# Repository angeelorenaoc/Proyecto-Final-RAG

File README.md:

# Proyecto-Final-RAG
Este proyecto tiene como objetivo desarrollar un robot guía autónomo para el pasillo del bloque 18 de la universidad. Diseñado para mejorar la experiencia de los estudiantes nuevos y visitantes, el robot proporcionará información útil y rutas. Él estará equipado con una pantalla OLED y un teclado, facilitando la interacción con los usuarios.

### Diagrama de Bloques: Estructura de Hardware

### Materiales 
  *  Pantalla OLED.
  *  Balizas: Antenas XBEE PRO.
  *  Raspberry Pi pico

### Diagrama de Flujo: Estructura del Código

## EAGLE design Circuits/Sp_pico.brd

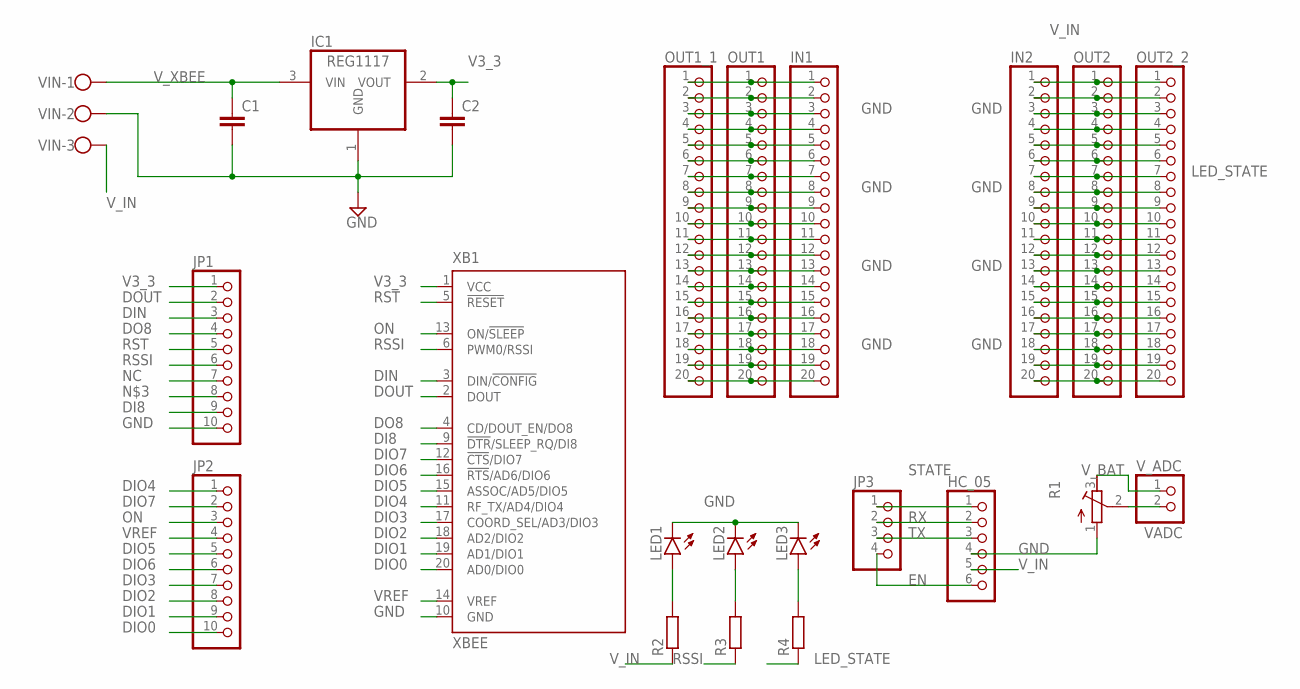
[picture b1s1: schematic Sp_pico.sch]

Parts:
C1, C2: C2.5/5; C2.5-5
HC_05: PINHD-1X6; 1X06
IC1: REG1117; SOT223
IN1, IN2: PINHD-1X20; 1X20
JP1, JP2: PINHD-1X10; 1X10
JP3: PINHD-1X4; 1X04
LED1, LED2, LED3: LED5MM
OUT1, OUT1_1, OUT2, OUT2_2: PINHD-1X20; 1X20
R1: R-TRIMM3296X; RTRIM3296X
R2, R3, R4: R-EU_0204/7; 0204/7
VIN: W237-103
V_ADC: PINHD-1X2; 1X02
XB1: XBEE

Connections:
DI8: JP1.9, XB1.9 (!DTR!/SLEEP_RQ/DI8)
DIN: JP1.3, XB1.3 (DIN/!CONFIG)
DIO0: JP2.10, XB1.20 (AD0/DIO0)
DIO1: JP2.9, XB1.19 (AD1/DIO1)
DIO2: JP2.8, XB1.18 (AD2/DIO2)
DIO3: JP2.7, XB1.17 (COORD_SEL/AD3/DIO3)
DIO4: JP2.1, XB1.11 (RF_TX/AD4/DIO4)
DIO5: JP2.5, XB1.15 (ASSOC/AD5/DIO5)
DIO6: JP2.6, XB1.16 (!RTS!/AD6/DIO6)
DIO7: JP2.2, XB1.12 (!CTS!/DIO7)
DO8: JP1.4, XB1.4 (CD/DOUT_EN/DO8)
DOUT: JP1.2, XB1.2 (DOUT)
EN: HC_05.6, JP3.4
GND: C1.2, C2.2, HC_05.4, IC1.1 (GND), IN1.3, IN1.8, IN1.13, IN1.18, IN2.3, IN2.8, IN2.13, IN2.18, JP1.10, LED1.K (C), LED2.K (C), LED3.K (C), OUT1.3, OUT1.8, OUT1.13, OUT1.18, OUT1_1.3, OUT1_1.8, OUT1_1.13, OUT1_1.18, OUT2.3, OUT2.8, OUT2.13, OUT2.18, OUT2_2.3, OUT2_2.8, OUT2_2.13, OUT2_2.18, R1.1 (A), VIN.2, XB1.10 (GND)
LED_STATE: IN2.7, OUT2.7, OUT2_2.7, R4.1
unnamed: IN1.1, OUT1.1, OUT1_1.1
unnamed: IN1.2, OUT1.2, OUT1_1.2
unnamed: IN1.4, OUT1.4, OUT1_1.4
unnamed: IN1.5, OUT1.5, OUT1_1.5
unnamed: IN1.6, OUT1.6, OUT1_1.6
unnamed: IN1.7, OUT1.7, OUT1_1.7
unnamed: LED1.A, R2.2
unnamed: IN1.9, OUT1.9, OUT1_1.9
unnamed: IN1.10, OUT1.10, OUT1_1.10
unnamed: IN1.11, OUT1.11, OUT1_1.11
unnamed: IN1.12, OUT1.12, OUT1_1.12
unnamed: LED2.A, R3.2
unnamed: IN1.14, OUT1.14, OUT1_1.14
unnamed: IN1.15, OUT1.15, OUT1_1.15
unnamed: IN1.16, OUT1.16, OUT1_1.16
unnamed: IN1.17, OUT1.17, OUT1_1.17
unnamed: LED3.A, R4.2
unnamed: IN1.19, OUT1.19, OUT1_1.19
unnamed: IN1.20, OUT1.20, OUT1_1.20
unnamed: IN2.2, OUT2.2, OUT2_2.2
unnamed: IN2.4, OUT2.4, OUT2_2.4
unnamed: IN2.5, OUT2.5, OUT2_2.5
unnamed: IN2.6, OUT2.6, OUT2_2.6
unnamed: IN2.9, OUT2.9, OUT2_2.9
unnamed: IN2.10, OUT2.10, OUT2_2.10
unnamed: IN2.11, OUT2.11, OUT2_2.11
unnamed: IN2.12, OUT2.12, OUT2_2.12
unnamed: IN2.14, OUT2.14, OUT2_2.14
unnamed: IN2.15, OUT2.15, OUT2_2.15
unnamed: IN2.16, OUT2.16, OUT2_2.16
unnamed: IN2.17, OUT2.17, OUT2_2.17
unnamed: IN2.19, OUT2.19, OUT2_2.19
unnamed: IN2.20, OUT2.20, OUT2_2.20
NC: JP1.7
ON: JP2.3, XB1.13 (ON/!SLEEP)
RSSI: JP1.6, R3.1, XB1.6 (PWM0/RSSI)
RST: JP1.5, XB1.5 (!RESET)
RX: HC_05.2, JP3.2
STATE: HC_05.1, JP3.1
TX: HC_05.3, JP3.3
V3_3: C2.1, IC1.2 (VOUT), JP1.1, XB1.1 (VCC)
VADC: R1.2 (S), V_ADC.2
VREF: JP2.4, XB1.14 (VREF)
V_BAT: R1.3 (E), V_ADC.1
V_IN: HC_05.5, IN2.1, OUT2.1, OUT2_2.1, R2.1, VIN.3
V_XBEE: C1.1, IC1.3 (VIN), VIN.1

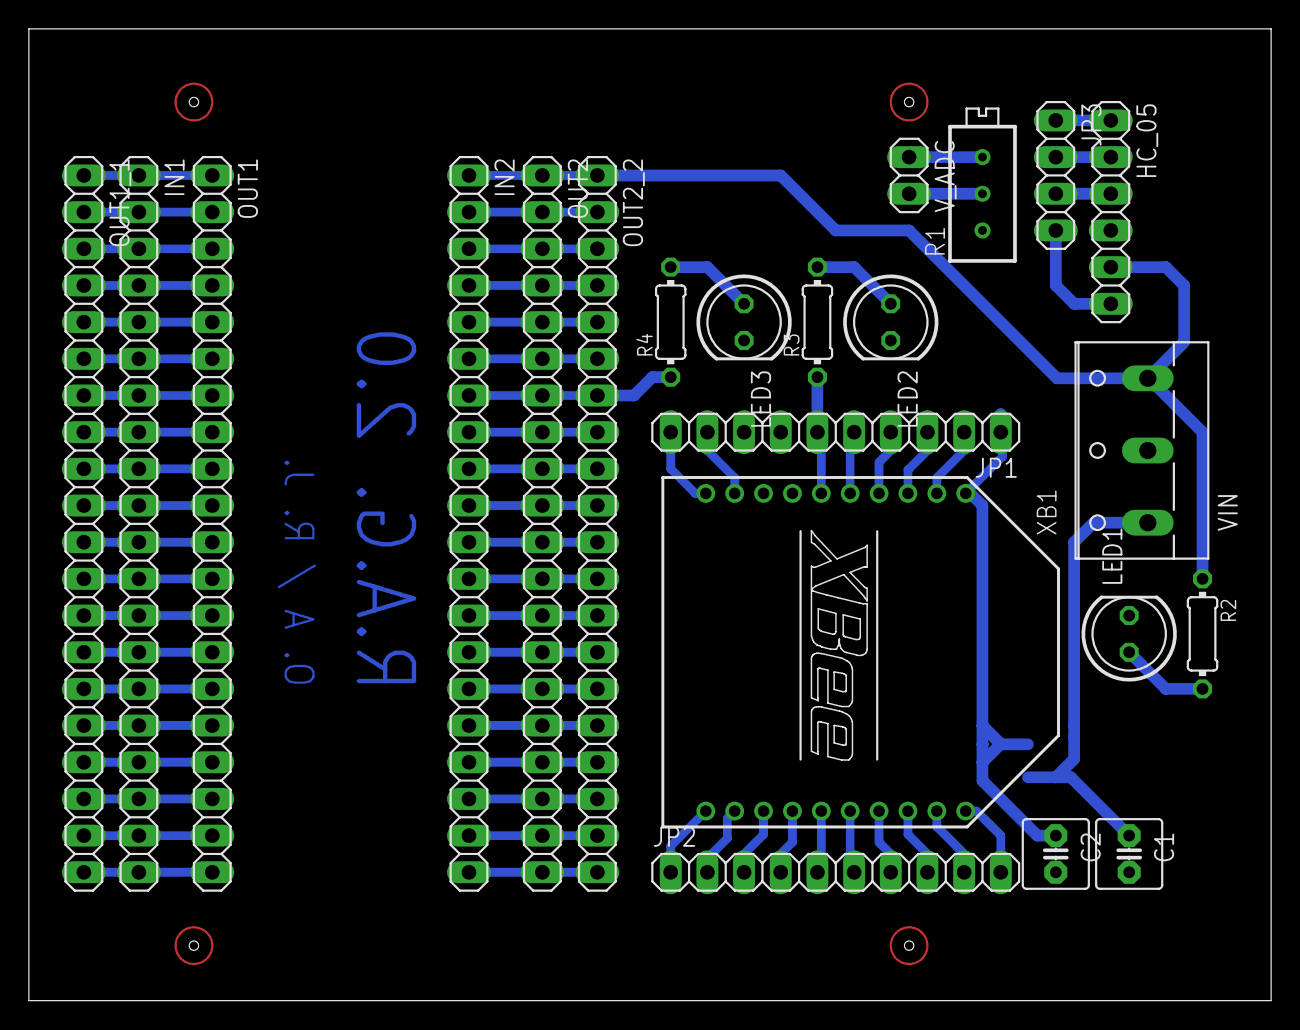
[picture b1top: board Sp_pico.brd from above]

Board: 2 copper layers, 86.0 x 67.3 mm, 23 parts (1 on the bottom side), 60 nets.

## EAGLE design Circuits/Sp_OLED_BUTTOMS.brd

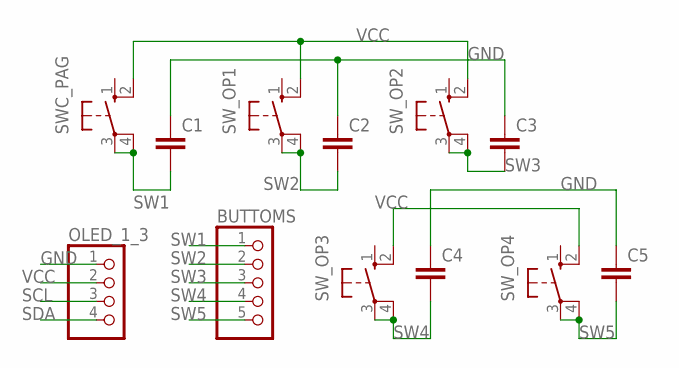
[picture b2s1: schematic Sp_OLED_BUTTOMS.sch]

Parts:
BUTTOMS: PINHD-1X5; 1X05
C1, C2, C3, C4, C5: C2,5-3; C2.5-3
OLED_1_3: PINHD-1X4; 1X04
SWC_PAG: 10-XX; B3F-10XX
SW_OP1, SW_OP2, SW_OP3, SW_OP4: 10-XX; B3F-10XX

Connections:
GND: C1.1, C2.1, C3.1, C4.1, C5.1, OLED_1_3.1
SCL: OLED_1_3.3
SDA: OLED_1_3.4
SW1: BUTTOMS.1, C1.2, SWC_PAG.3, SWC_PAG.4 (P1)
SW2: BUTTOMS.2, C2.2, SW_OP1.3, SW_OP1.4 (P1)
SW3: BUTTOMS.3, C3.2, SW_OP2.3, SW_OP2.4 (P1)
SW4: BUTTOMS.4, C4.2, SW_OP3.3, SW_OP3.4 (P1)
SW5: BUTTOMS.5, C5.2, SW_OP4.3, SW_OP4.4 (P1)
VCC: OLED_1_3.2, SWC_PAG.2 (S1), SW_OP1.2 (S1), SW_OP2.2 (S1), SW_OP3.2 (S1), SW_OP4.2 (S1)

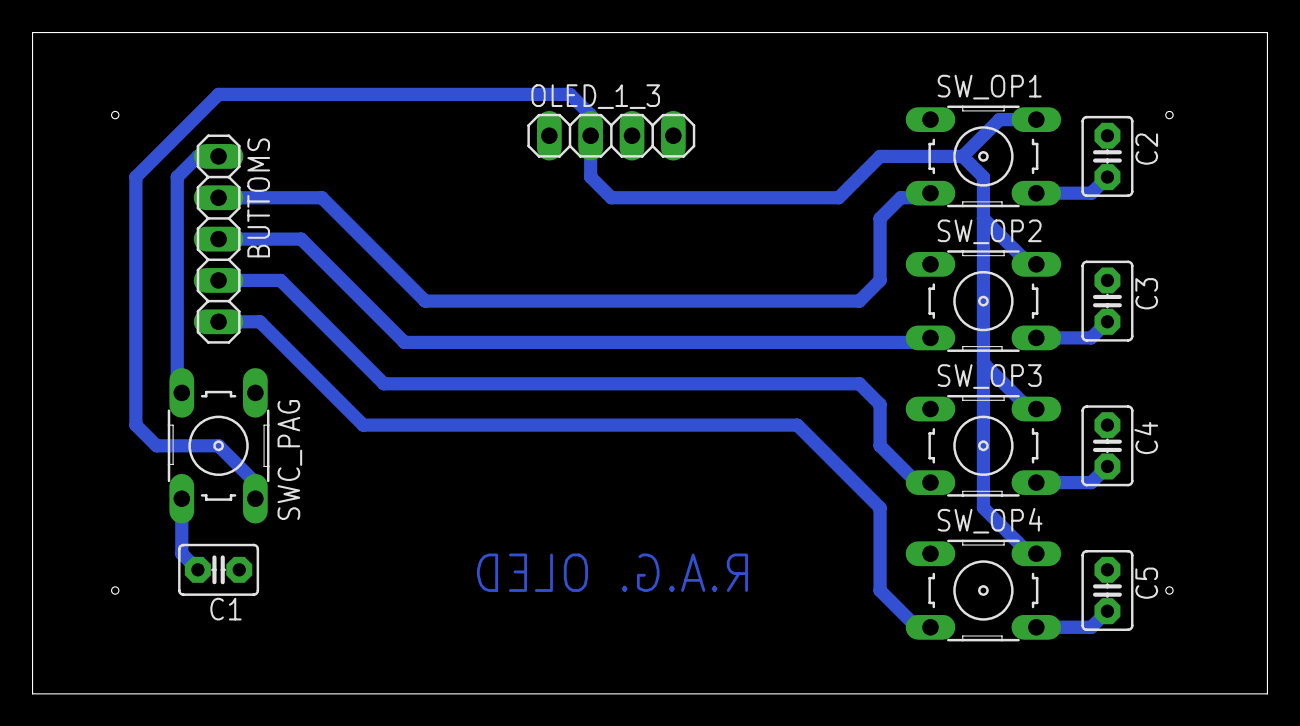
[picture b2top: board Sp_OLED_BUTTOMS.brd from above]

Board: 2 copper layers, 75.9 x 40.6 mm, 12 parts (0 on the bottom side), 7 nets.

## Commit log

2024-11-19 Se agrega Cronograma de actividades y los diagramas de flujo tentativos del desarrollo del proyecto
2024-11-19 Se agrega la libreria para el uso y control de la pantalla OLED escrita por Larry Bank (bitbank@pobox.com), extraida de https://wokwi.com/projects/393154286020492289
2024-11-19 Update README.md
    Actualización de las descripción del proyecto
2024-11-19 Update README.md
    Actualización del README con la descripción del proyecto
2024-11-20 Uart-DMA
2024-11-20 Ejemplo Uart-DMA
    Prueba de comunicación mediante UART y traspaso a través del DMA
2024-11-20 Update base
2024-12-01 Configuración de la comunicación mediante el UART y estimación de la potencia de las balizas a través del PWM. Además de desarrollar la función que se encarga de la triangulación.
2024-12-01 Se actualiza el cronograma con las actividades realizadas durante la semana
2024-12-06 Ajustes en la triangulación y configuración de los GPIOs para la salidas de los motores
2024-12-06 Integración de animaciones, menus, y demás aspectos para ser mostrados en la pantalla
2024-12-06 Descartando archivos innecesarios
2024-12-07 Se añaden los diseños de PCBs a usar
2024-12-08 Unión del menú con la triangulación y desarrollo del seguidor de línea
2024-12-12 Unificación del menú, con la comunicación bluetooth, y ajustes en la triangulación y el seguidor de línea
2024-12-12 Pruebas en el control de motores
2024-12-13 Eliminación de funciones innecesarias, se agregan comentarios al código y se ajustan los umbrales
